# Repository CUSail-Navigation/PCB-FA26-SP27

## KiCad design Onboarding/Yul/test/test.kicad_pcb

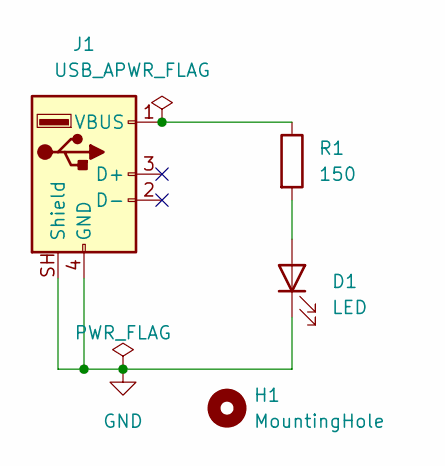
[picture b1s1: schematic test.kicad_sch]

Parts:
D1: LED; LED_0402_1005Metric_Pad0.77x0.64mm_HandSolder
H1: MountingHole; MountingHole_2.1mm
J1: USB_A; USB3_A_Molex_48393-001
R1: 150; R_0603_1608Metric

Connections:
GND: D1.1 (K), J1.4 (GND), J1.SH (Shield)
unnamed: D1.2 (A), R1.2
unnamed: J1.1 (VBUS), R1.1

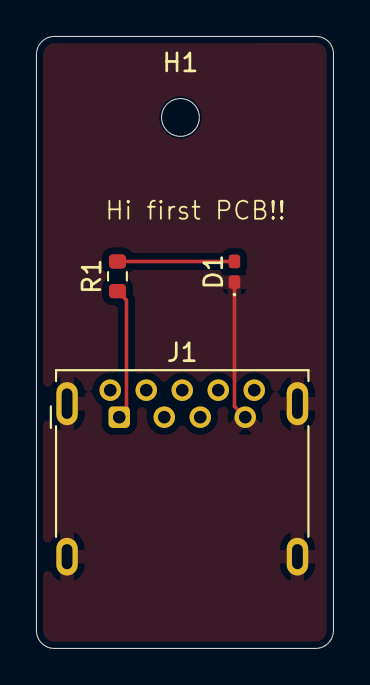
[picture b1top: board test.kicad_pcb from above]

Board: 2 copper layers, 16.5 x 34.0 mm, 4 parts (0 on the bottom side), 3 nets.

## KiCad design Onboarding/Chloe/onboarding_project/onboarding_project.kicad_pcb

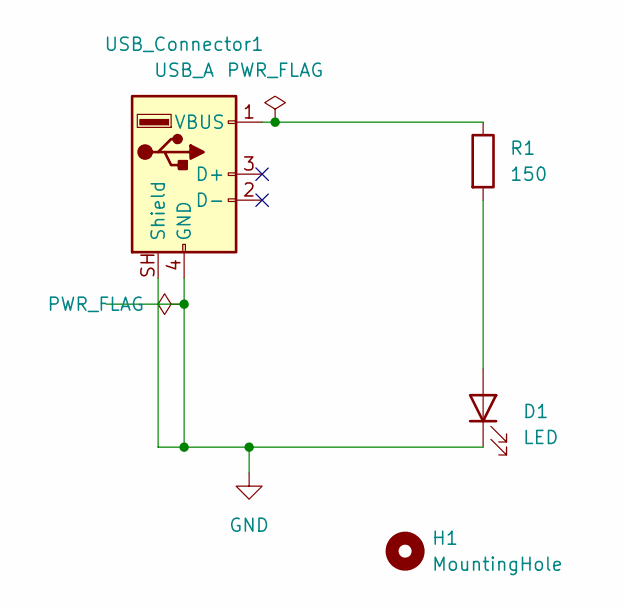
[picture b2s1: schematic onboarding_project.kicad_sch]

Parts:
D1: LED; LED_0402_1005Metric_Pad0.77x0.64mm_HandSolder
H1: MountingHole; MountingHole_2.1mm
R1: 150; R_0603_1608Metric
USB_Connector1: USB_A; USB3_A_Molex_48393-001

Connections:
GND: D1.1 (K), USB_Connector1.4 (GND), USB_Connector1.SH (Shield)
unnamed: D1.2 (A), R1.2
unnamed: R1.1, USB_Connector1.1 (VBUS)

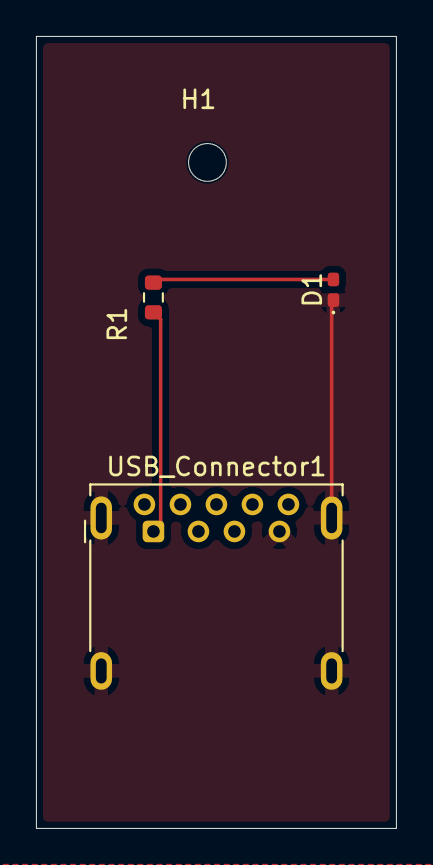
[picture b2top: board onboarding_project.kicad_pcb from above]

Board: 2 copper layers, 20.0 x 44.0 mm, 4 parts (0 on the bottom side), 3 nets.

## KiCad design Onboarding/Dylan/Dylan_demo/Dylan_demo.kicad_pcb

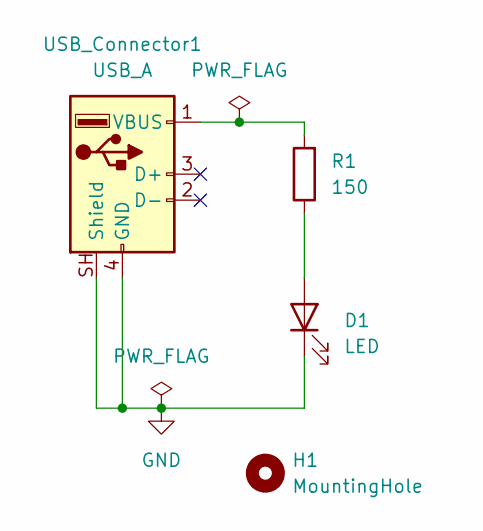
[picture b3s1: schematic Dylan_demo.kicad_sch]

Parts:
D1: LED; LED_0402_1005Metric_Pad0.77x0.64mm_HandSolder
H1: MountingHole; MountingHole_2.1mm
R1: 150; R_0603_1608Metric
USB_Connector1: USB_A; USB3_A_Molex_48393-001

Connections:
GND: D1.1 (K), USB_Connector1.4 (GND), USB_Connector1.SH (Shield)
unnamed: D1.2 (A), R1.1
unnamed: R1.2, USB_Connector1.1 (VBUS)

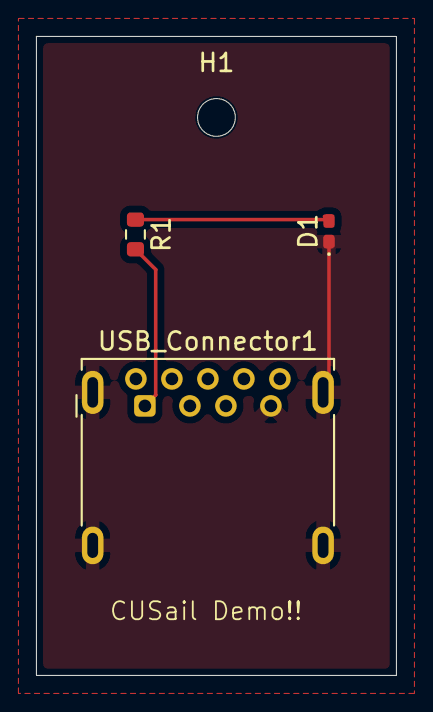
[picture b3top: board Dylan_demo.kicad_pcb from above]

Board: 2 copper layers, 20.0 x 35.5 mm, 4 parts (0 on the bottom side), 3 nets.

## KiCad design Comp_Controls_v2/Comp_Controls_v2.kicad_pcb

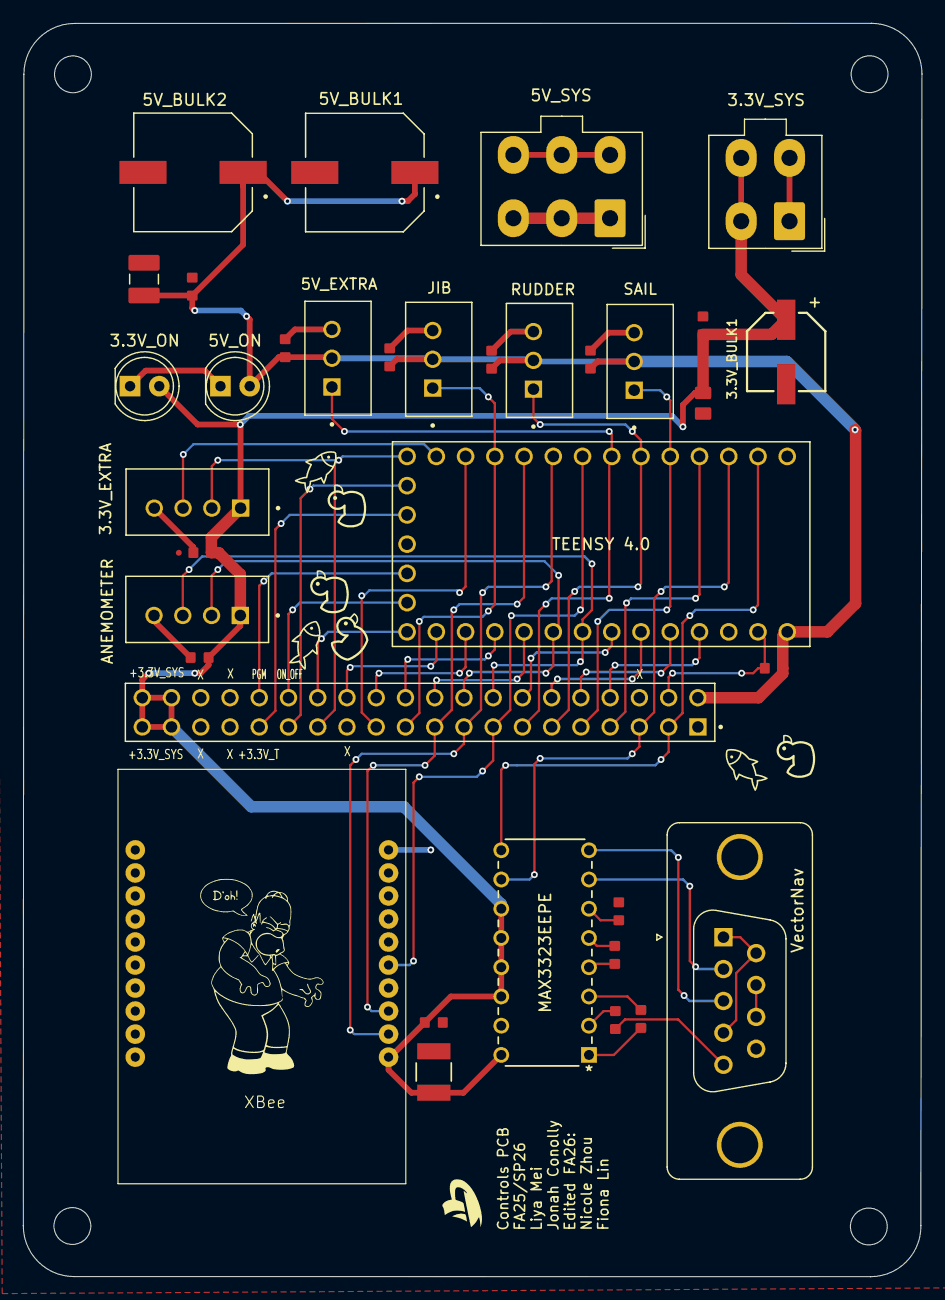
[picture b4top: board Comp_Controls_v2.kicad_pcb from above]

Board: 2 copper layers, 78.1 x 108.9 mm, 39 parts (0 on the bottom side), 41 nets.

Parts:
3.3V_BULK1: 220uf; CAP_87510_220uf
3.3V_EXTRA: B4B-XH-A
3.3V_LOW1, 5V_LOW1: 0.1uf; CAP_CL10B_01uf_0603
3.3V_MID1: 10uf; CAP_CL21A_10uf_0805
3.3V_ON: 3.3v_LED; LED_D5.0mm
3.3V_SYS: Conn_02x02_Counter_Clockwise; Molex_Mini-Fit_Jr_5566-04A_2x02_P4.20mm_Vertical
5V_BULK1, 5V_BULK2: 1000uf; CAP_EEE1A_1000uf
5V_EXTRA: B3B-XH-A
5V_MID1: 22uf; CAP_CL32A_22uf_1210
5V_ON: 5v_LED; LED_D5.0mm
5V_SYS: Conn_02x03_Counter_Clockwise; Molex_Mini-Fit_Jr_5566-06A_2x03_P4.20mm_Vertical
ANEMOMETER: B4B-XH-A
C1, C2, C3, C4, C6, C7, C8, C9, C10, C11, C12: 0.1µF; CAP_CL10B_01uf_0603
C5: 47µF; CAP_C3225_47uf_1210
H1, H1#2, H1#3, H1#4: MountingHole; MountingHole_3.2mm_M3
HEADERS1: M20-7832046; HARWIN_M20-7832046
JIB: B3B-XH-A
MAX3323EEPE: max3323eepe+; MAX3323EEPE+
RUDDER: B3B-XH-A
SAIL: B3B-XH-A
TEENSY 4.0: DEV-15583; MODULE_DEV-15583
TeensyC0.1: 0.1µF; CAP_CL10B_01uf_0603
VectorNav: DE9_Socket_MountingHoles; DSUB-9_Socket_Vertical_P2.77x2.84mm_MountingHoles
XBEE1: XBee

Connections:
2: HEADERS1.7, TEENSY 4.0.2
3.3v_extra: HEADERS1.23, TEENSY 4.0.10
5v_extra: 5V_EXTRA.1, HEADERS1.13, TEENSY 4.0.5
13: HEADERS1.28, TEENSY 4.0.13
14: HEADERS1.26, TEENSY 4.0.14
15: HEADERS1.24, TEENSY 4.0.15
16: HEADERS1.22, TEENSY 4.0.16
17: HEADERS1.20, TEENSY 4.0.17
20: HEADERS1.14, TEENSY 4.0.20
21: HEADERS1.12, TEENSY 4.0.21
22: HEADERS1.10, TEENSY 4.0.22
23: HEADERS1.8, TEENSY 4.0.23
+3.3V_SYS: 3.3V_BULK1.1, 3.3V_EXTRA.1, 3.3V_LOW1.1, 3.3V_MID1.1, 3.3V_ON.2 (A), 3.3V_SYS.2, 3.3V_SYS.4, ANEMOMETER.1, C4.1, C5.1, C8.1, C10.1, HEADERS1.37, HEADERS1.38, HEADERS1.39, HEADERS1.40, MAX3323EEPE.11 (TXENABLE), MAX3323EEPE.12 (RENABLE), MAX3323EEPE.13 (VL), MAX3323EEPE.14 (*SHDN), MAX3323EEPE.16 (VCC), XBEE1.1 (VCC)
+5V_SYS1: 5V_BULK1.1, 5V_BULK2.1, 5V_EXTRA.2, 5V_LOW1.2, 5V_MID1.2, 5V_ON.2 (A), 5V_SYS.1, 5V_SYS.2, 5V_SYS.3, C7.1, C9.1, C11.1, C12.1, HEADERS1.2, JIB.2, RUDDER.2, SAIL.2, TEENSY 4.0.VIN, TeensyC0.1.2
Extra40: 3.3V_EXTRA.2, HEADERS1.27, TEENSY 4.0.12
Extra41: 3.3V_EXTRA.3, TEENSY 4.0.11
GND: 3.3V_BULK1.2, 3.3V_EXTRA.4, 3.3V_LOW1.2, 3.3V_MID1.2, 3.3V_ON.1 (K), 3.3V_SYS.1, 3.3V_SYS.3, 5V_BULK1.2, 5V_BULK2.2, 5V_EXTRA.3, 5V_LOW1.1, 5V_MID1.1, 5V_ON.1 (K), 5V_SYS.4, 5V_SYS.5, 5V_SYS.6, ANEMOMETER.4, C2.2, C4.2, C5.2, C6.1, C7.2, C8.2, C9.2, C10.2, C11.2, C12.2, HEADERS1.1, HEADERS1.4, JIB.3, MAX3323EEPE.15 (GND), RUDDER.3, SAIL.3, TEENSY 4.0.G3, TeensyC0.1.1, VectorNav.5, XBEE1.10 (GND)
JIB: HEADERS1.21, JIB.1, TEENSY 4.0.9
unnamed: C3.1, MAX3323EEPE.1 (C1+)
unnamed: C3.2, MAX3323EEPE.3 (C1-)
unnamed: C1.1, MAX3323EEPE.4 (C2+)
unnamed: C1.2, MAX3323EEPE.5 (C2-)
unnamed: C6.2, MAX3323EEPE.2 (V+)
unnamed: C2.1, MAX3323EEPE.6 (V-)
unnamed: VectorNav.1, VectorNav.4, VectorNav.6
unnamed: VectorNav.7, VectorNav.8
ON_OFF: HEADERS1.30, TEENSY 4.0.ON-OFF (ON/OFF)
PGM: HEADERS1.32, TEENSY 4.0.PGM (PROGRAM)
Rudder: HEADERS1.11, RUDDER.1, TEENSY 4.0.4
Sail: HEADERS1.9, SAIL.1, TEENSY 4.0.3
TEENSY_3.3V: HEADERS1.31, TEENSY 4.0.3.3V_1
TeensyRX: HEADERS1.3, MAX3323EEPE.9 (ROUT1), TEENSY 4.0.0
TeensyTX: HEADERS1.5, MAX3323EEPE.10 (TIN1), TEENSY 4.0.1
VBAT: HEADERS1.29, TEENSY 4.0.VBAT
VectorNavRX: MAX3323EEPE.7 (TOUT1), VectorNav.2
VectorNavTX: MAX3323EEPE.8 (RIN1), VectorNav.3
WindData0: ANEMOMETER.2, HEADERS1.18, TEENSY 4.0.18
WindData1: ANEMOMETER.3, HEADERS1.16, TEENSY 4.0.19
XBeeRESET: HEADERS1.15, TEENSY 4.0.6, XBEE1.5 (RESET)
XBeeRX: HEADERS1.19, TEENSY 4.0.8, XBEE1.3 (DIN/CONFIG)
XBeeTX: HEADERS1.17, TEENSY 4.0.7, XBEE1.2 (DOUT)
